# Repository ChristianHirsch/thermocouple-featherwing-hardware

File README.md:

# Thermocouple FeatherWing Hardware

This hardware is used to connect a K-type thermocouple to Adafruit Feather boards. It uses the MAX31855 thermocouple to digital converter.

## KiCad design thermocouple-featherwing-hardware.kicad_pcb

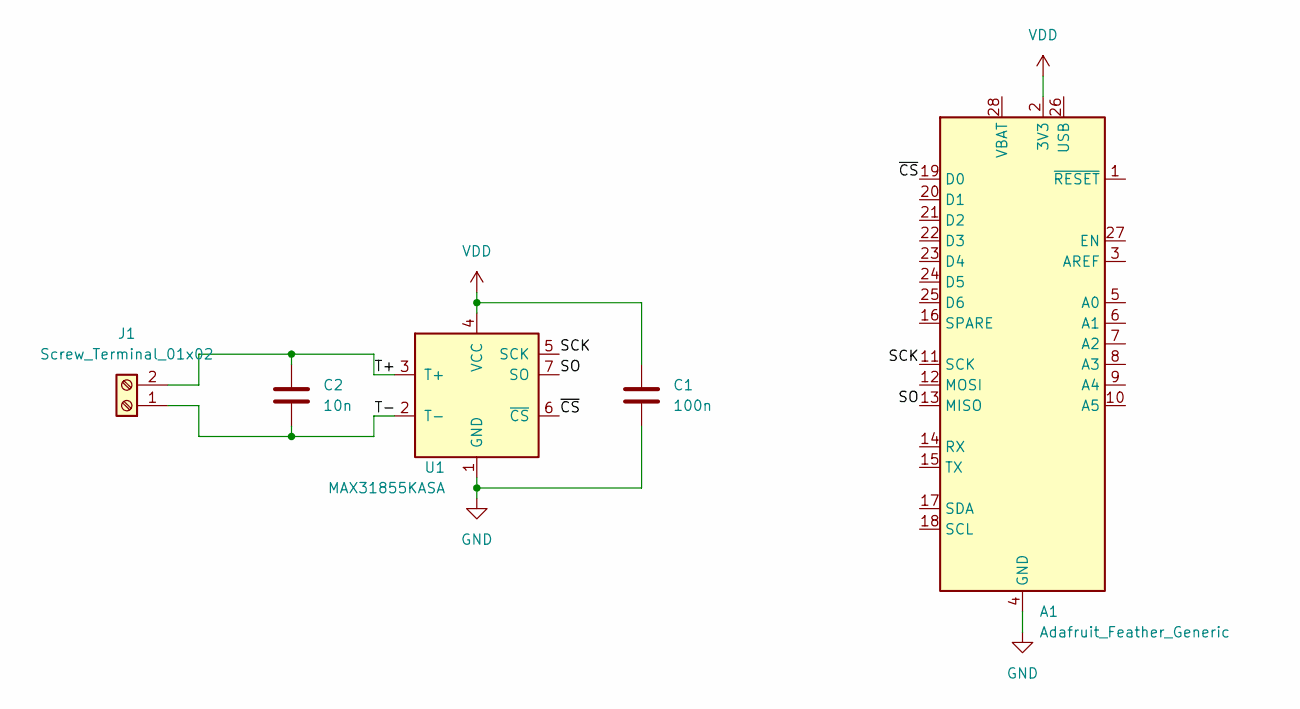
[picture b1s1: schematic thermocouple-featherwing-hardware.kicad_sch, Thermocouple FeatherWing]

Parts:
A1: Adafruit_Feather_Generic; Adafruit_Feather_EdgeCuts
C1: 100n; C_0603_1608Metric
C2: 10n; C_0603_1608Metric
J1: Screw_Terminal_01x02; PhoenixContact_MSTBA_2,5_2-G_1x02_P5.00mm_Horizontal
U1: MAX31855KASA; SOIC-8_3.9x4.9mm_P1.27mm

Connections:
/SCK: A1.11 (SCK), U1.5 (SCK)
/SO: A1.13 (MISO), U1.7 (SO)
/T+: C2.1, J1.2, U1.3 (T+)
/T-: C2.2, J1.1, U1.2 (T-)
/~CS: A1.19 (D0), U1.6 (~CS)
GND: A1.4 (GND), C1.2, U1.1 (GND)
VDD: A1.2 (3V3), C1.1, U1.4 (VCC)

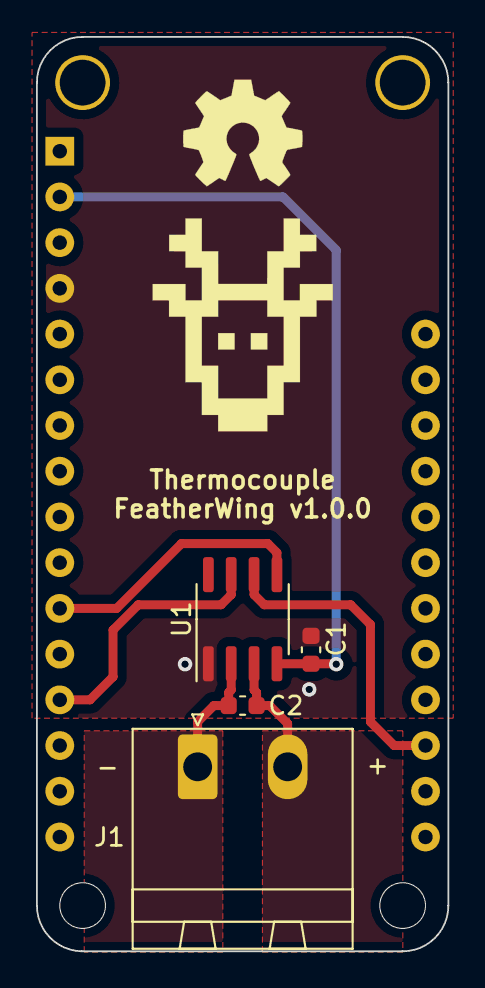
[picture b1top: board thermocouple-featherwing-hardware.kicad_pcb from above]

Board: 2 copper layers, 22.9 x 50.8 mm, 5 parts (0 on the bottom side), 7 nets.

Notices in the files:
thermocouple-featherwing-hardware.kicad_pcb:
Copyright (c) 2023 Christian Hirsch
SPDX-License-Identifier: Apache-2.0 WITH SHL-2.1
